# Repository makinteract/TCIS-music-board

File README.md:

# TCIS-music-board

A simple board to make music with a 555 timer. Designed with [KiCad](https://kicad.org/).

Video: [YouTube](./assets/overview.jpg)

## Schematic diagram

Here the full schematics: [schematics and board](./schematics_board.pdf)

### Bill of Material

| Part              | Notes                                                           |
| ----------------- | --------------------------------------------------------------- |
| 9V battery        |                                                                 |
| Battery case      |                                                                 |
| R1 330K           |                                                                 |
| R2 10K            |                                                                 |
| C1 100n           |                                                                 |
| C2 470p           |                                                                 |
| C3 1u             |                                                                 |
| Piezo Speaker     | Like [GEC17C](https://www.devicemart.co.kr/goods/view?no=25043) |
| NE555             |                                                                 |
| Alligator clips   |                                                                 |
| Headers (100 mil) |                                                                 |

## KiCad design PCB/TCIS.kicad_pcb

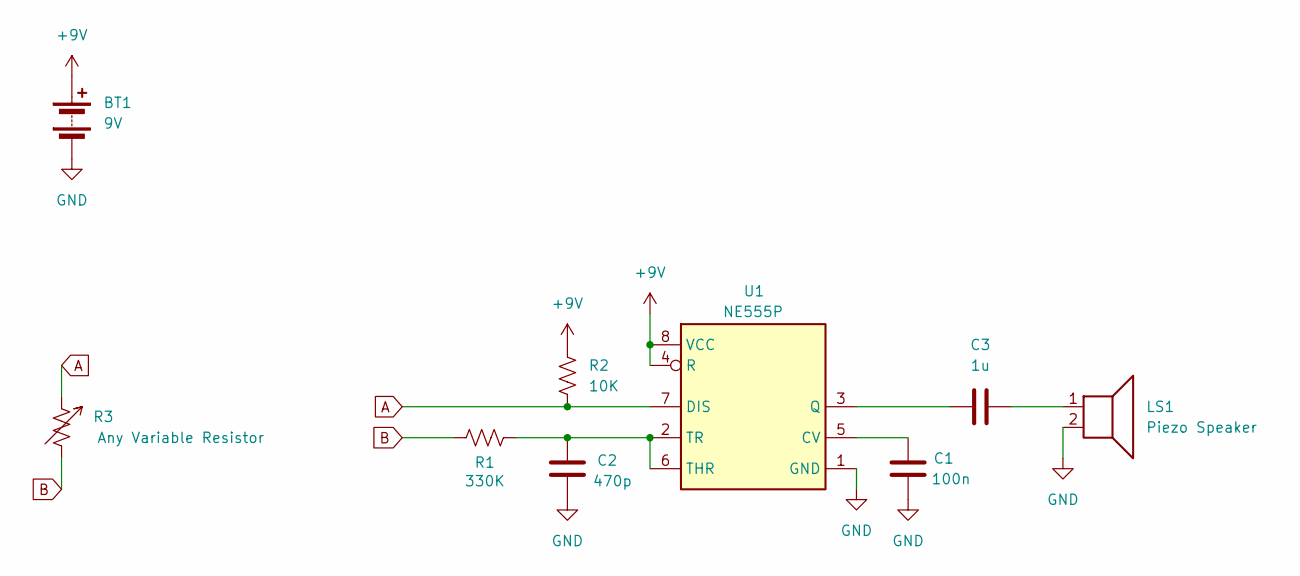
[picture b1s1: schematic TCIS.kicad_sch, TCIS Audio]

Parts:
BT1: 9V; PinHeader_1x02_P2.54mm_Vertical
C1: 100n; C_Axial_L3.8mm_D2.6mm_P7.50mm_Horizontal
C2: 470p; C_Axial_L3.8mm_D2.6mm_P7.50mm_Horizontal
C3: 1u; C_Axial_L3.8mm_D2.6mm_P7.50mm_Horizontal
LS1: Piezo Speaker; Speaker
R1: 330K; R_Axial_DIN0207_L6.3mm_D2.5mm_P10.16mm_Horizontal
R2: 10K; R_Axial_DIN0207_L6.3mm_D2.5mm_P10.16mm_Horizontal
R3: Any Variable Resistor; PinHeader_1x02_P2.54mm_Horizontal
U1: NE555P; DIP-8_W7.62mm

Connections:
+9V: BT1.1 (+), R2.1, U1.4 (R), U1.8 (VCC)
A: R2.2, R3.1, U1.7 (DIS)
B: R1.2, R3.2
GND: BT1.2 (-), C1.2, C2.2, LS1.2, U1.1 (GND)
unnamed: C3.2, LS1.1
unnamed: C1.1, U1.5 (CV)
unnamed: C3.1, U1.3 (Q)
unnamed: C2.1, R1.1, U1.2 (TR), U1.6 (THR)

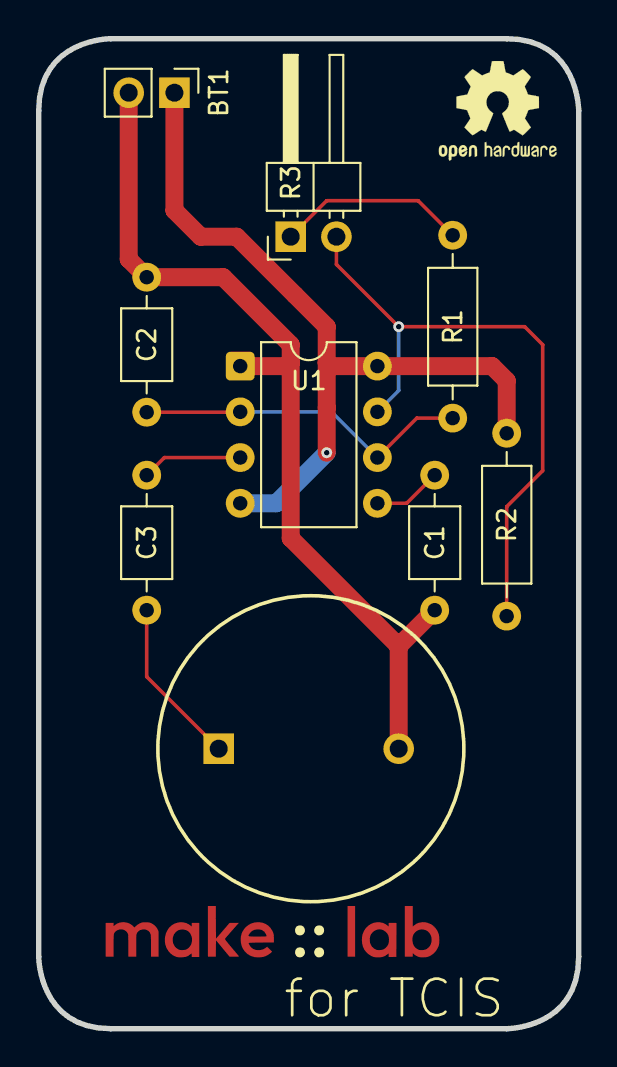
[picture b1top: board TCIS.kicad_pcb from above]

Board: 2 copper layers, 30.0 x 55.0 mm, 9 parts (0 on the bottom side), 8 nets.

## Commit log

2025-03-17 uploading files
2025-03-17 ignoring some fiels
2025-04-15 Updated PCB
2025-04-15 Added video
2025-04-16 Adding slides
2025-06-17 Updated BoM
